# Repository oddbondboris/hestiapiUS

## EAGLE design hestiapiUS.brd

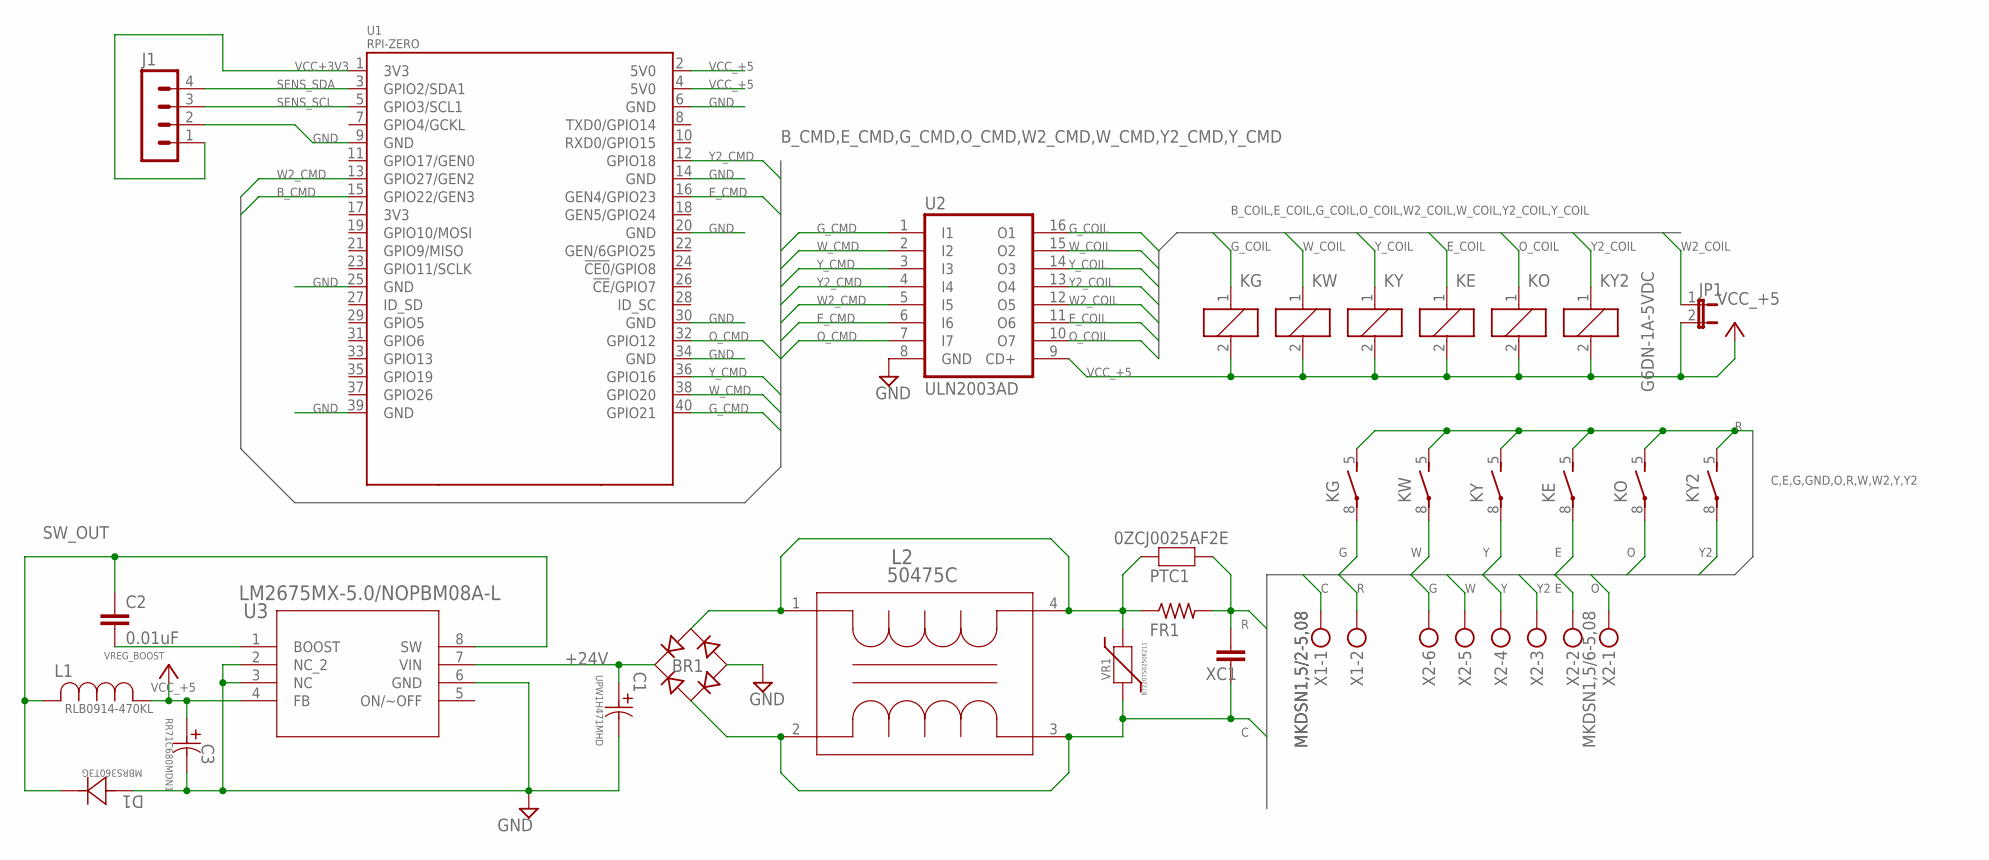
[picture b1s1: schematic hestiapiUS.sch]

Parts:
BR1: DF06S; DFS
C1: UPW1H471MHD; PCAP_12_5X20-THRU-ELECT
C2: 0.01uF; 0603
C3: RR71C680MDN1; RR-A
D1: MBRS360T3G; DIODE_SMC_7P15X6P25
FR1: R-US_0207/12; 0207/12
J1: MA04-1
JP1: JP1E; JP1
KE: G6DN-1A-5VDC; G6DN
KG: G6DN-1A-5VDC; G6DN
KO: G6DN-1A-5VDC; G6DN
KW: G6DN-1A-5VDC; G6DN
KY, KY2: G6DN-1A-5VDC; G6DN
L1: RLB0914-470KL; IND_BOURNS_RLB0914
L2: 50475C; IND_50XXXC
PTC1: 0ZCJ0025AF2E; 0ZCJ
U1: RPI-ZERO; RASPBERRYPI_BASTELSTUBE_V13_RASPI_BOARD_B+_FULL
U2: ULN2003AD; SO16
U3: LM2675MX-5.0/NOPBM08A-L; M08A-L
VR1: B72207S0250K211; VARISTOR7MM
X1: MKDSN1,5/2-5,08
X2: MKDSN1,5/6-5,08
XC1: C-EU025-024X044; C025-024X044

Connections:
+24V: BR1.+, C1.1, U3.7 (VIN)
+24_FUSED: BR1.AC2, FR1.1, L2.1, L2.4, PTC1.1, VR1.2
B_CMD: U1.15 (GPIO22/GEN3)
C: BR1.AC1, L2.2, L2.3, VR1.1, X1.1, XC1.2
E: KE.8, X2.2
E_CMD: U1.16 (GEN4/GPIO23), U2.6 (I6)
E_COIL: KE.1, U2.11 (O6)
G: KG.8, X2.6
GND: BR1.-, C1.2, C3.2, D1.2, J1.2, U1.6 (GND), U1.9 (GND), U1.14 (GND), U1.20 (GND), U1.25 (GND), U1.30 (GND), U1.34 (GND), U1.39 (GND), U2.8 (GND), U3.2 (NC_2), U3.3 (NC), U3.6 (GND)
G_CMD: U1.40 (GPIO21), U2.1 (I1)
G_COIL: KG.1, U2.16 (O1)
O: KO.8, X2.1
O_CMD: U1.32 (GPIO12), U2.7 (I7)
O_COIL: KO.1, U2.10 (O7)
R: FR1.2, KE.5 (S), KG.5 (S), KO.5 (S), KW.5 (S), KY.5 (S), KY2.5 (S), PTC1.2, X1.2, XC1.1
SENS_SCL: J1.3, U1.5 (GPIO3/SCL1)
SENS_SDA: J1.4, U1.3 (GPIO2/SDA1)
SW_OUT: C2.1, D1.1, L1.2, U3.8 (SW)
VCC+3V3: J1.1, U1.1 (3V3)
VCC_+5: C3.1, JP1.2, KE.2, KG.2, KO.2, KW.2, KY.2, KY2.2, L1.1, U1.2 (5V0), U1.4 (5V0), U2.9 (CD+), U3.4 (FB)
VREG_BOOST: C2.2, U3.1 (BOOST)
W: KW.8, X2.5
W2_CMD: U1.13 (GPIO27/GEN2), U2.5 (I5)
W2_COIL: JP1.1, U2.12 (O5)
W_CMD: U1.38 (GPIO20), U2.2 (I2)
W_COIL: KW.1, U2.15 (O2)
Y: KY.8, X2.4
Y2: KY2.8, X2.3
Y2_CMD: U1.12 (GPIO18), U2.4 (I4)
Y2_COIL: KY2.1, U2.13 (O4)
Y_CMD: U1.36 (GPIO16), U2.3 (I3)
Y_COIL: KY.1, U2.14 (O3)

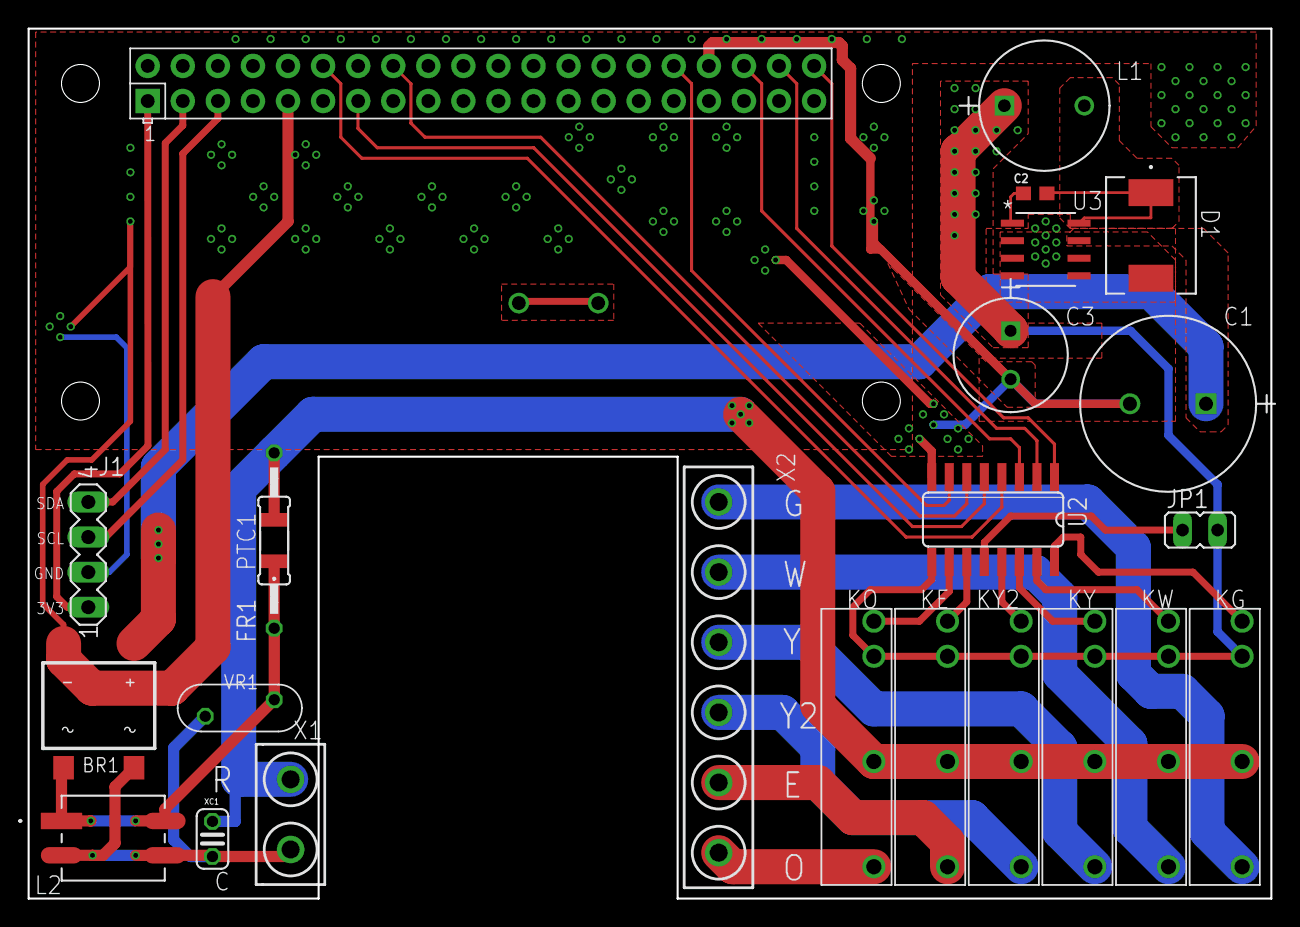
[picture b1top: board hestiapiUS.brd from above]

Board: 2 copper layers, 90.0 x 63.0 mm, 24 parts (0 on the bottom side), 31 nets.

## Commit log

2019-10-01 higher res image
2019-10-02 fix library pathing and add library
2019-10-02 update image
